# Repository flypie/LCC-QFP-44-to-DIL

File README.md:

# LCC-QFP-44-to-DIL
A Simple PCB that can convert between 44 pin QFP & LCC to DIL for use with breadboards etc.

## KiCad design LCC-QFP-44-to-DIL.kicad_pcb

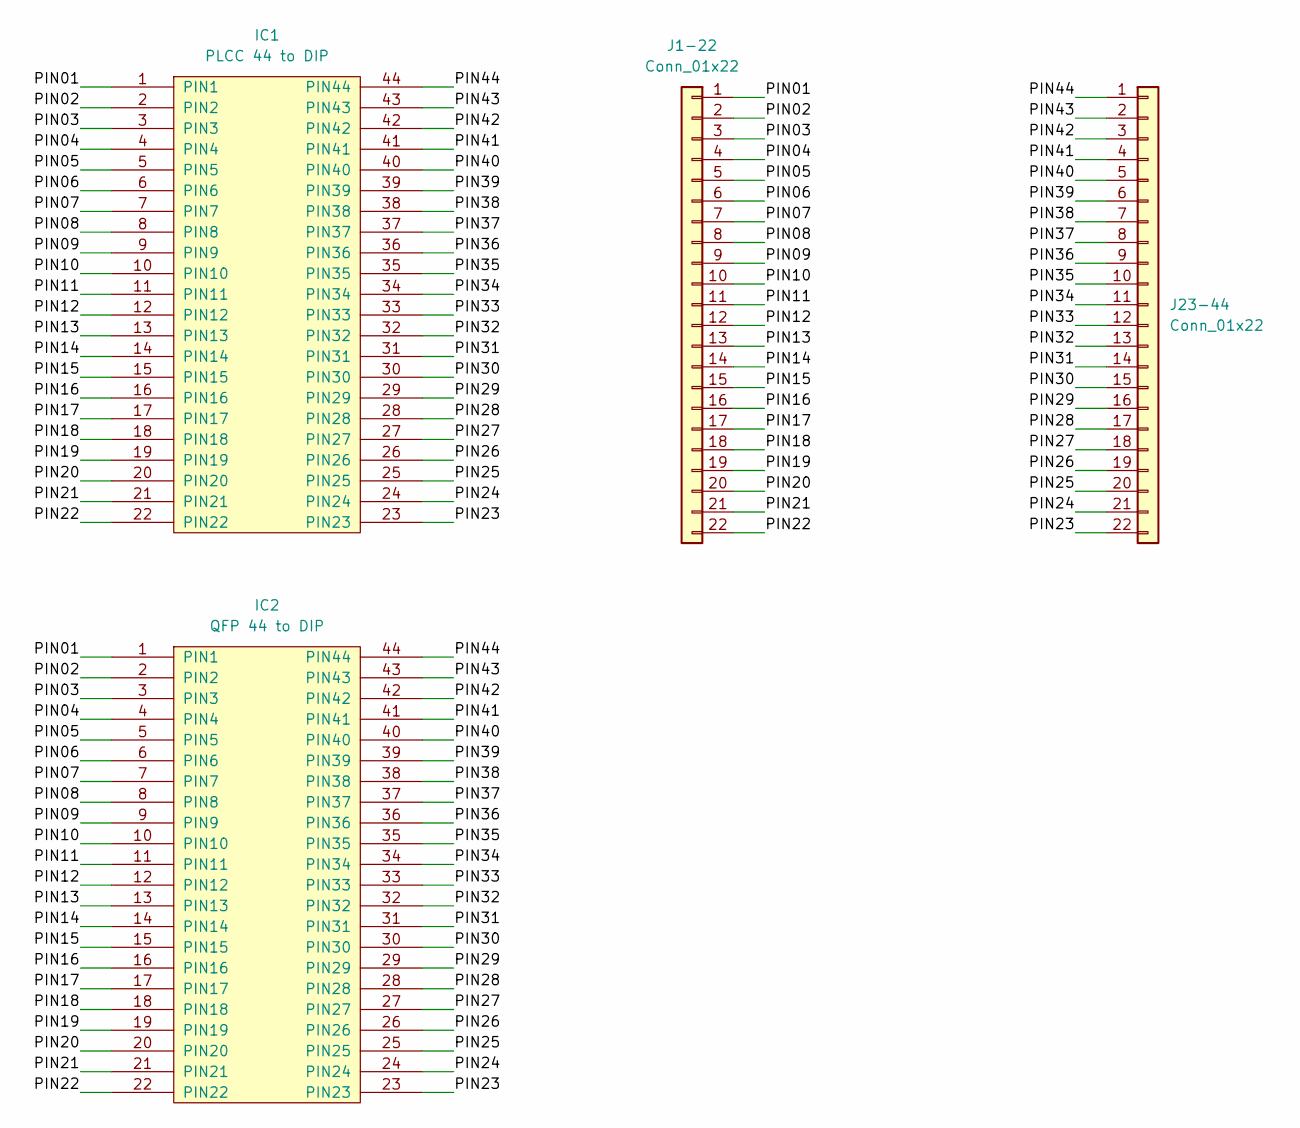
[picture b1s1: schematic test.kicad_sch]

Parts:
IC1: PLCC 44 to DIP; PLCC-44_THT-Socket; Mouser Part Number 804-GLS29EE010-70PHE
IC2: QFP 44 to DIP; PQFP-44_10x10mm_P0.8mm; Mouser Part Number 804-GLS29EE010-70PHE
J1-22, J23-44: Conn_01x22; PinHeader_1x22_P2.54mm_Vertical

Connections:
/PIN01: IC1.1 (PIN1), IC2.1 (PIN1), J1-22.1
/PIN02: IC1.2 (PIN2), IC2.2 (PIN2), J1-22.2
/PIN03: IC1.3 (PIN3), IC2.3 (PIN3), J1-22.3
/PIN04: IC1.4 (PIN4), IC2.4 (PIN4), J1-22.4
/PIN05: IC1.5 (PIN5), IC2.5 (PIN5), J1-22.5
/PIN06: IC1.6 (PIN6), IC2.6 (PIN6), J1-22.6
/PIN07: IC1.7 (PIN7), IC2.7 (PIN7), J1-22.7
/PIN08: IC1.8 (PIN8), IC2.8 (PIN8), J1-22.8
/PIN09: IC1.9 (PIN9), IC2.9 (PIN9), J1-22.9
/PIN10: IC1.10 (PIN10), IC2.10 (PIN10), J1-22.10
/PIN11: IC1.11 (PIN11), IC2.11 (PIN11), J1-22.11
/PIN12: IC1.12 (PIN12), IC2.12 (PIN12), J1-22.12
/PIN13: IC1.13 (PIN13), IC2.13 (PIN13), J1-22.13
/PIN14: IC1.14 (PIN14), IC2.14 (PIN14), J1-22.14
/PIN15: IC1.15 (PIN15), IC2.15 (PIN15), J1-22.15
/PIN16: IC1.16 (PIN16), IC2.16 (PIN16), J1-22.16
/PIN17: IC1.17 (PIN17), IC2.17 (PIN17), J1-22.17
/PIN18: IC1.18 (PIN18), IC2.18 (PIN18), J1-22.18
/PIN19: IC1.19 (PIN19), IC2.19 (PIN19), J1-22.19
/PIN20: IC1.20 (PIN20), IC2.20 (PIN20), J1-22.20
/PIN21: IC1.21 (PIN21), IC2.21 (PIN21), J1-22.21
/PIN22: IC1.22 (PIN22), IC2.22 (PIN22), J1-22.22
/PIN23: IC1.23 (PIN23), IC2.23 (PIN23), J23-44.22
/PIN24: IC1.24 (PIN24), IC2.24 (PIN24), J23-44.21
/PIN25: IC1.25 (PIN25), IC2.25 (PIN25), J23-44.20
/PIN26: IC1.26 (PIN26), IC2.26 (PIN26), J23-44.19
/PIN27: IC1.27 (PIN27), IC2.27 (PIN27), J23-44.18
/PIN28: IC1.28 (PIN28), IC2.28 (PIN28), J23-44.17
/PIN29: IC1.29 (PIN29), IC2.29 (PIN29), J23-44.16
/PIN30: IC1.30 (PIN30), IC2.30 (PIN30), J23-44.15
/PIN31: IC1.31 (PIN31), IC2.31 (PIN31), J23-44.14
/PIN32: IC1.32 (PIN32), IC2.32 (PIN32), J23-44.13
/PIN33: IC1.33 (PIN33), IC2.33 (PIN33), J23-44.12
/PIN34: IC1.34 (PIN34), IC2.34 (PIN34), J23-44.11
/PIN35: IC1.35 (PIN35), IC2.35 (PIN35), J23-44.10
/PIN36: IC1.36 (PIN36), IC2.36 (PIN36), J23-44.9
/PIN37: IC1.37 (PIN37), IC2.37 (PIN37), J23-44.8
/PIN38: IC1.38 (PIN38), IC2.38 (PIN38), J23-44.7
/PIN39: IC1.39 (PIN39), IC2.39 (PIN39), J23-44.6
/PIN40: IC1.40 (PIN40), IC2.40 (PIN40), J23-44.5
/PIN41: IC1.41 (PIN41), IC2.41 (PIN41), J23-44.4
/PIN42: IC1.42 (PIN42), IC2.42 (PIN42), J23-44.3
/PIN43: IC1.43 (PIN43), IC2.43 (PIN43), J23-44.2
/PIN44: IC1.44 (PIN44), IC2.44 (PIN44), J23-44.1

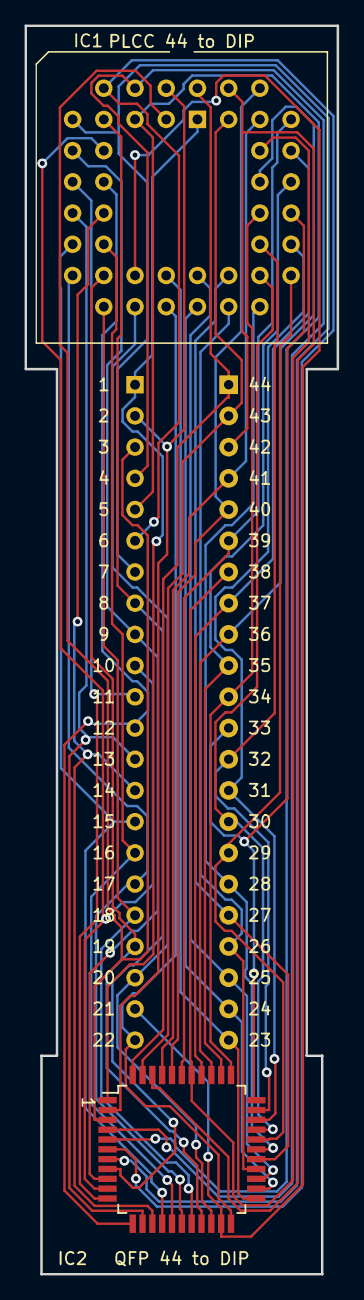
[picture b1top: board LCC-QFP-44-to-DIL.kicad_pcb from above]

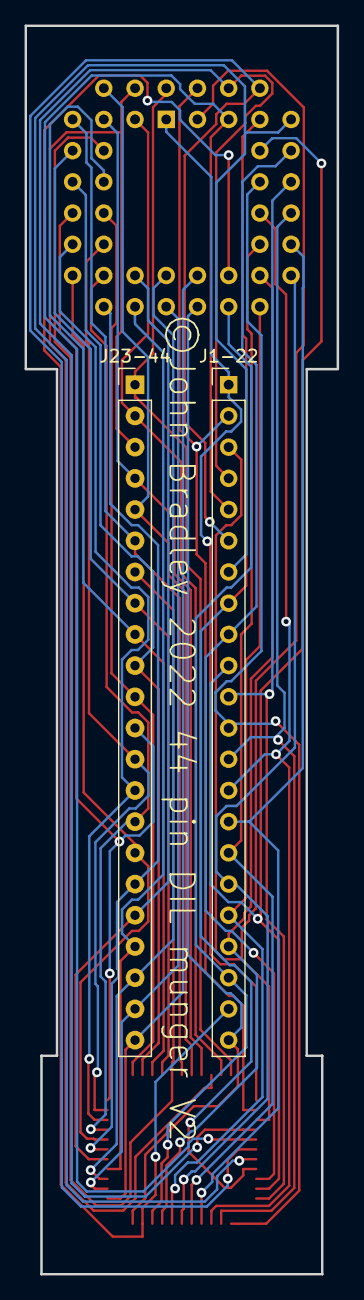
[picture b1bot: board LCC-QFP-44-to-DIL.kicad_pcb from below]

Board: 2 copper layers, 25.4 x 101.6 mm, 4 parts (2 on the bottom side), 44 nets.

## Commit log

2022-05-05 Correct Names.
2022-05-05 add gerbers.

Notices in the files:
LCC-QFP-44-to-DIL.kicad_pcb:
©John Bradley 2022 44 pin DIL munger V2
